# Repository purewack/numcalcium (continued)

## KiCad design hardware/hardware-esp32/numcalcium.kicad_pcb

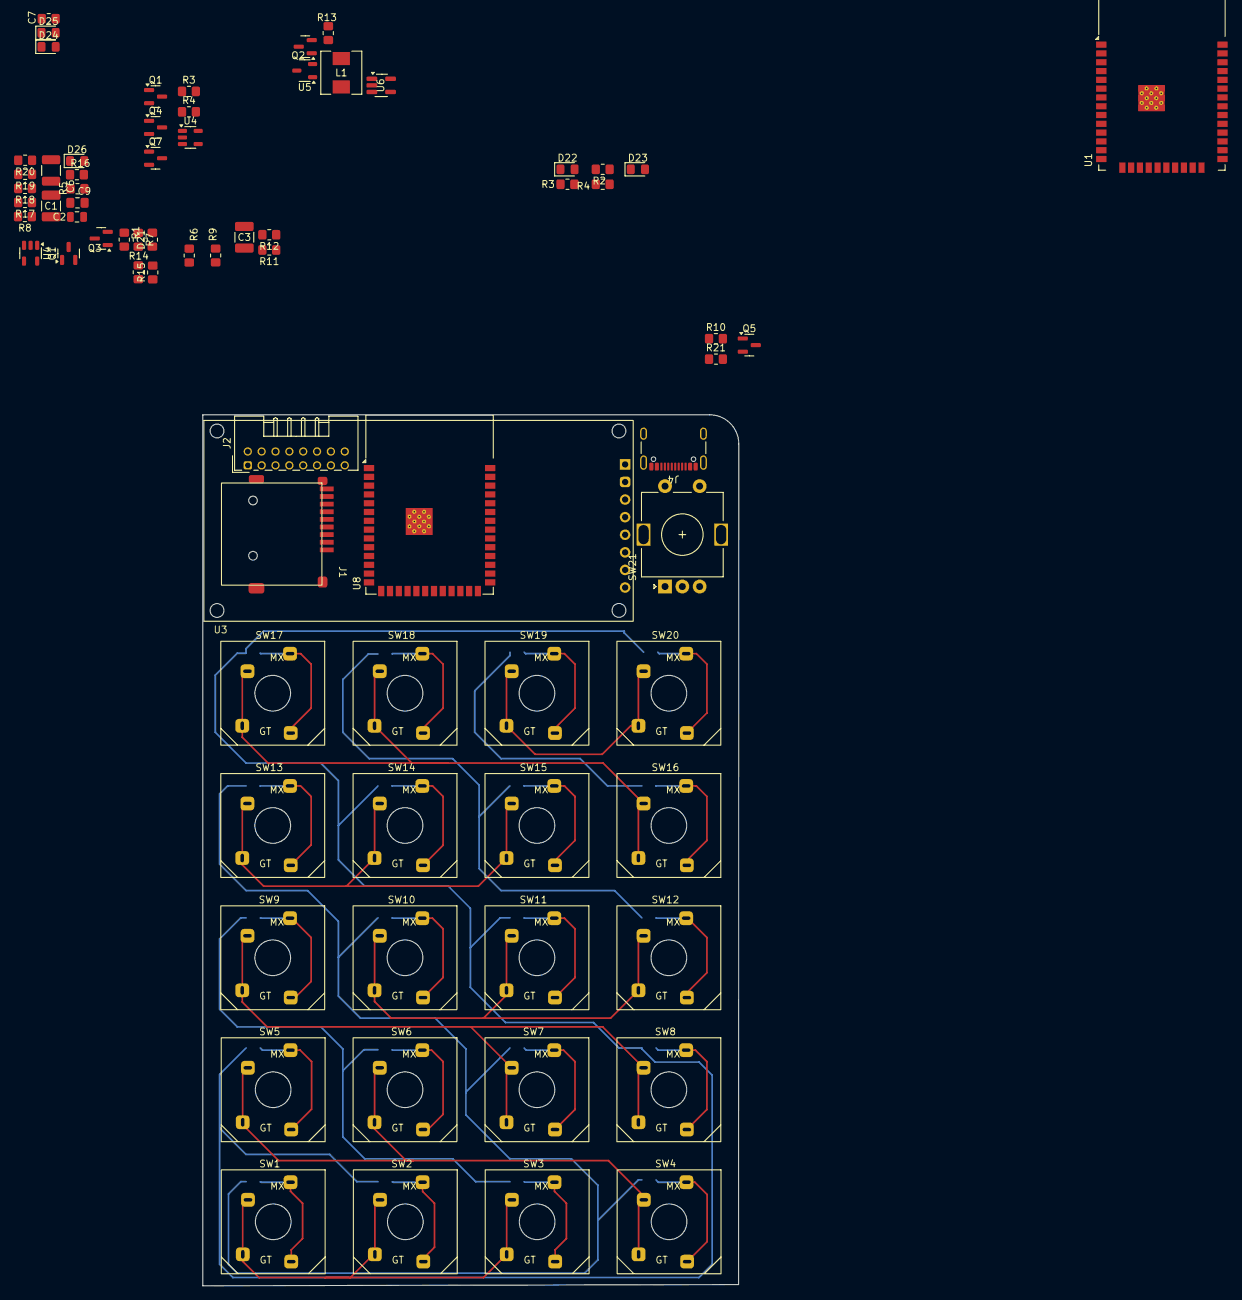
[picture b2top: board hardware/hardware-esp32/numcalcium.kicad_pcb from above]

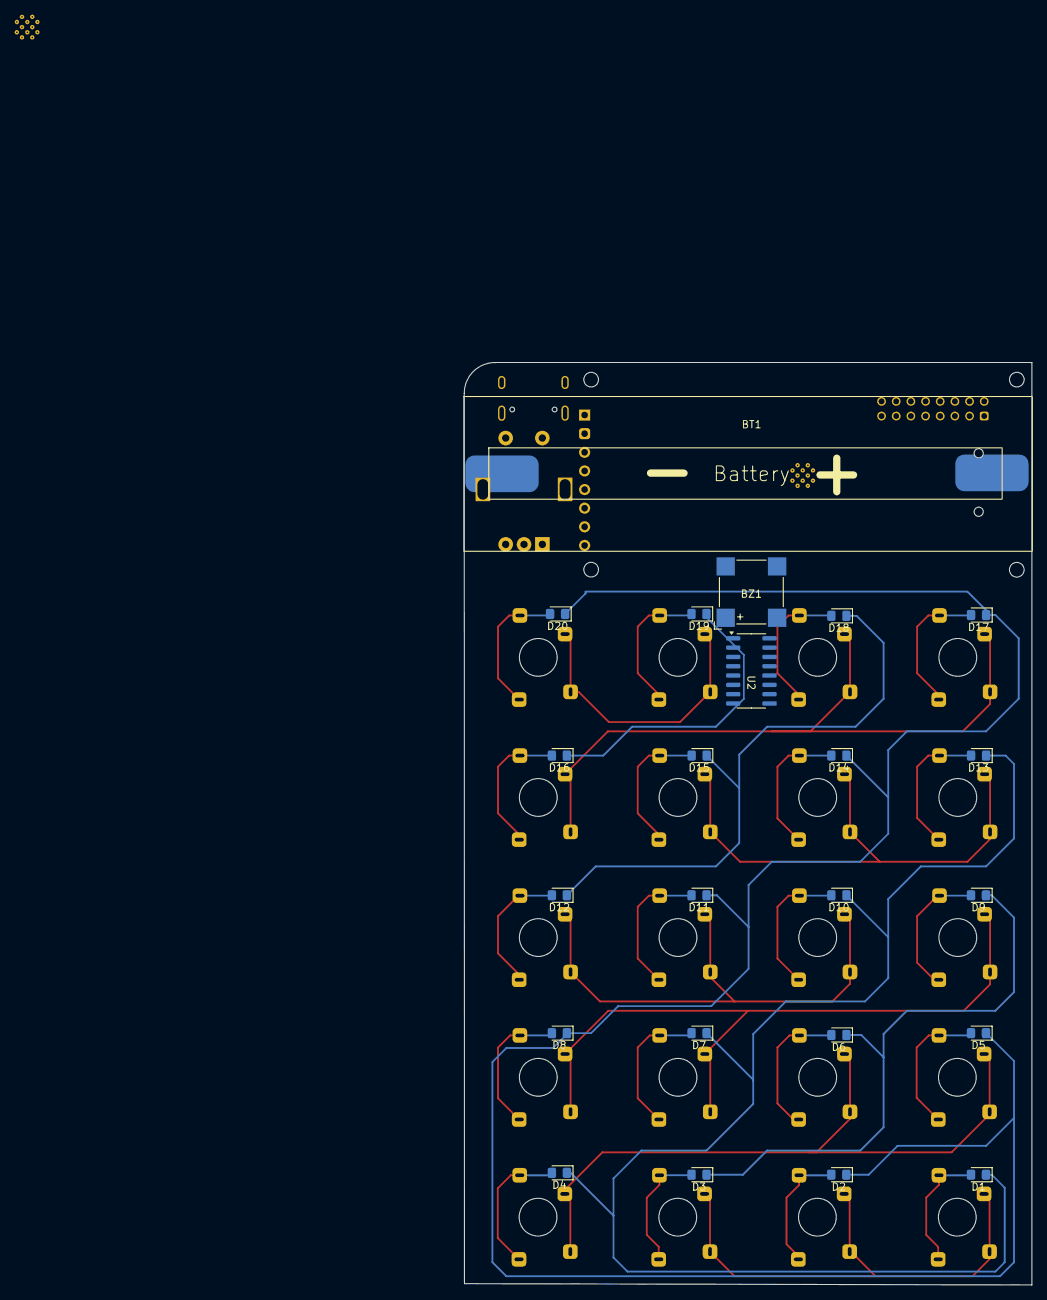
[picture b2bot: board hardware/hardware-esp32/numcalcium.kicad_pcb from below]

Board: 2 copper layers, 77.4 x 125.8 mm, 97 parts (23 on the bottom side), 69 nets.

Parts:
BT1: Battery; LiIon18650
BZ1: Buzzer; MagneticBuzzer_CUI_CMT-8504-100-SMT
C1: 10u; C_1210_3225Metric_Pad1.33x2.70mm_HandSolder
C2: 100n; C_0805_2012Metric
C3: 22u; C_1210_3225Metric_Pad1.33x2.70mm_HandSolder
C6: 22u; R_1210_3225Metric_Pad1.30x2.65mm_HandSolder
C7: 100n; R_0805_2012Metric_Pad1.20x1.40mm_HandSolder
C9: 22u; C_0805_2012Metric_Pad1.18x1.45mm_HandSolder
D1, D2, D3, D4, D5, D6, D7, D8, D9, D10, D11, D12, D13, D14, D15, D16, D17, D18, D19, D20, D22, D23, D24, D25, D26: D; D_0805_2012Metric_Pad1.15x1.40mm_HandSolder
D21: BAT_REV; R_0805_2012Metric_Pad1.20x1.40mm_HandSolder
J1: Micro_SD_Card_Det2; microSD_Short_1
J2: Conn_02x08_Counter_Clockwise; JAE_LY20-16P-DLT1_2x08_P2.00mm_Horizontal
J4: USB_C_Receptacle_USB2.0_16P; USB_C_Receptacle_GCT_USB4105-xx-A_16P_TopMnt_Horizontal
L1: 2u2; L_Chilisin_BMRA00050530
Q1, Q1#2, Q4, Q7: AO3401A; SOT-23
Q2, Q3, Q5: BSS138; SOT-23
R1, R2, R11, R12: 100k; R_0805_2012Metric_Pad1.20x1.40mm_HandSolder
R3, R3#2, R4, R4#2: 5k6; R_0805_2012Metric_Pad1.20x1.40mm_HandSolder
R5: 2k; R_0805_2012Metric_Pad1.20x1.40mm_HandSolder
R6: 220k; R_0805_2012Metric_Pad1.20x1.40mm_HandSolder
R7: 33k; R_0805_2012Metric_Pad1.20x1.40mm_HandSolder
R8, R9, R17, R18, R19, R20: 47k; R_0805_2012Metric_Pad1.20x1.40mm_HandSolder
R10, R15, R21: 10k; R_0805_2012Metric_Pad1.20x1.40mm_HandSolder
R13, R14, R16: 1M; R_0805_2012Metric_Pad1.20x1.40mm_HandSolder
SW1, SW2, SW3, SW4, SW5, SW6, SW7, SW8, SW9, SW10, SW11, SW12, SW13, SW14, SW15, SW16, SW17, SW18, SW19, SW20: SW_Push; Combo_MechanicalSwitch
SW21: Encoder; RotaryEncoder_Alps_EC11E-Switch_Vertical_H20mm
U1: ESP32-WROOM-32D
U2: 74HC595; SOIC-16_3.9x9.9mm_P1.27mm
U3: ISP Display; ST7789 1.9inch module Display
U4, U4#2: LTC4054ES5-4.2; TSOT-23-5
U5: XC6206PxxxMR; SOT-23-3
U6: STI3411A; SOT-23-5_HandSoldering
U8: ESP32-S3-WROOM-1

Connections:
/Power/VBAT_MON: R13.2, R14.1
/Power/VCART: C6.1, C7.1, Q1.3 (D), Q1#2.3 (D)
/Power/VCART_ON: Q1.1 (G), Q1#2.1 (G), R11.2
/Power/VDD_AON: C9.1, L1.2, R6.1, U5.2 (VO)
/Power/VPOW_OFF: Q4.1 (G), R16.2, U6.1 (EN)
B_OK: R2.2, SW21.S1, U1.25 (IO0)
CART_FEED: R12.1, SW19.2, SW20.2, U2.1 (QB)
CART_SENSE: D24.2 (A), R12.2
GND: BT1.2 (-), C1.2, C2.2, C3.2, C6.2, C7.2, C9.2, D21.2 (A), J1.6 (VSS), J1.11 (SHIELD), J4.A1 (GND), J4.A12 (GND), J4.B1 (GND), J4.B12 (GND), Q2.2 (S), Q3.2 (S), Q5.2 (S), Q7.1 (G), R3.2, R3#2.2, R4.2, R4#2.2, R5.2, R9.2, R14.2, SW21.S2, U1.1 (GND), U1.15 (GND), U1.38 (GND), U1.39 (GND), U2.8 (GND), U3.1 (GND), U4.2 (GND), U4#2.2 (GND), U5.1 (GND), U6.2 (GND)
IO_CK: D1.1 (K), D4.1 (K), D7.1 (K), D10.1 (K), D13.1 (K), D16.1 (K), D19.1 (K), D22.1 (K), U1.8 (IO32), U2.11 (SRCLK)
IO_D: D2.1 (K), D5.1 (K), D8.1 (K), D11.1 (K), D14.1 (K), D17.1 (K), D20.1 (K), D23.1 (K), U1.9 (IO33), U2.14 (SER)
IO_OE: Q2.1 (G), U1.12 (IO27), U2.12 (RCLK)
IO_T: D3.1 (K), D6.1 (K), D9.1 (K), D12.1 (K), D15.1 (K), D18.1 (K), D24.1 (K), D25.1 (K), U1.6 (IO34)
unnamed: BT1.1 (+), Q7.3 (D), R7.1
unnamed: BZ1.2 (-), D26.2 (A), Q3.3 (D)
unnamed: D1.2 (A), SW1.1
unnamed: D2.2 (A), SW2.1
unnamed: D3.2 (A), SW3.1
unnamed: D4.2 (A), SW4.1
unnamed: D5.2 (A), SW5.1
unnamed: D6.2 (A), SW6.1
unnamed: D7.2 (A), SW7.1
unnamed: D8.2 (A), SW8.1
unnamed: D9.2 (A), SW9.1
unnamed: D10.2 (A), SW10.1
unnamed: D11.2 (A), SW11.1
unnamed: D12.2 (A), SW12.1
unnamed: D13.2 (A), SW13.1
unnamed: D14.2 (A), SW14.1
unnamed: D15.2 (A), SW15.1
unnamed: D16.2 (A), SW16.1
unnamed: D17.2 (A), SW17.1
unnamed: D18.2 (A), SW18.1
unnamed: D19.2 (A), SW19.1
unnamed: D20.2 (A), SW20.1
unnamed: D21.1 (K), R7.2
unnamed: D22.2 (A), SW21.A
unnamed: D23.2 (A), SW21.B
unnamed: J1.5 (CLK), U1.13 (IO14), U3.3 (CK)
unnamed: J1.3 (CMD), R18.2, U1.23 (IO15), U3.4 (D)
unnamed: J1.7 (DAT0), R19.2, U1.24 (IO2)
unnamed: J1.8 (DAT1), R20.2, U1.26 (IO4), U3.6 (DC)
unnamed: J1.1 (DAT2), R8.2, U1.14 (IO12)
unnamed: J1.2 (DAT3/CD), R17.2, U1.16 (IO13)
unnamed: J4.A5 (CC1), R3.1, R3#2.1
unnamed: J4.B5 (CC2), R4.1, R4#2.1
unnamed: C3.1, Q1.2 (S), Q1#2.2 (S), Q4.2 (S), Q7.2 (S), R11.1, R13.1, R16.1, U4.3 (BAT), U4#2.3 (BAT), U6.4 (VIN)
unnamed: Q2.3 (D), R1.2, U2.13 (~OE)
unnamed: Q3.1 (G), R15.2
unnamed: Q4.3 (D), U5.3 (VI)
unnamed: Q5.3 (D), U3.8 (LIGHT)
unnamed: Q5.1 (G), R10.2
unnamed: R21.1, U1.3 (EN)
unnamed: U1.28 (IO17), U3.7 (CS)
unnamed: R10.1, U1.5 (SENSOR_VN)
unnamed: SW16.2, SW17.2, SW18.2, U2.2 (QC)
unnamed: SW13.2, SW14.2, SW15.2, U2.3 (QD)
unnamed: SW10.2, SW11.2, SW12.2, U2.4 (QE)
unnamed: SW7.2, SW8.2, SW9.2, U2.5 (QF)
unnamed: SW4.2, SW5.2, SW6.2, U2.6 (QG)
unnamed: SW1.2, SW2.2, SW3.2, U2.7 (QH)
unnamed: R5.1, U4.5 (PROG), U4#2.5 (PROG)
unnamed: C1.1, C2.1, J4.A4 (VBUS), J4.A9 (VBUS), J4.B4 (VBUS), J4.B9 (VBUS), U4.4 (V_{CC}), U4#2.4 (V_{CC})
unnamed: R6.2, R9.1
unnamed: L1.1, U6.3 (LX)
unnamed: U8.1 (GND), U8.40 (GND), U8.41 (GND)
SD_FEED: SW21.C, U2.15 (QA)
SD_SENSE: D25.2 (A), J1.9 (DET_B)
VDD: BZ1.1 (+), D26.1 (K), J1.4 (VDD), R1.1, R8.1, R17.1, R18.1, R19.1, R20.1, R21.2, U1.2 (VDD), U2.10 (~SRCLR), U2.16 (VCC), U3.2 (VDD)

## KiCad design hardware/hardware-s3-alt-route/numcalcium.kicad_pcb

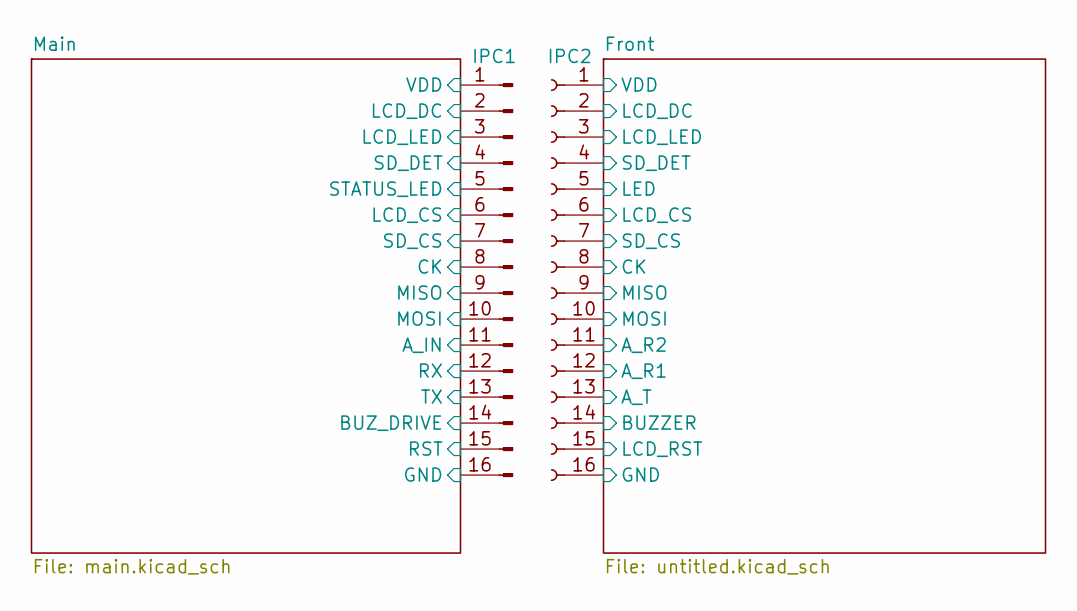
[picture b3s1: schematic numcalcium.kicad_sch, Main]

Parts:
IPC1: Conn_01x16_Pin; PinHeader_1x16_P2.54mm_Vertical
IPC2: Conn_01x16_Socket; PinSocket_1x16_P2.54mm_Vertical

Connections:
/Front/A_R1: IPC2.12; also elsewhere on the board
/Front/A_R2: IPC2.11; also elsewhere on the board
/Front/A_T: IPC2.13; also elsewhere on the board
/Front/BUZZER: IPC2.14; also elsewhere on the board
/Front/CK: IPC2.8; also elsewhere on the board
/Front/LCD_CS: IPC2.6; also elsewhere on the board
/Front/LCD_DC: IPC2.2; also elsewhere on the board
/Front/LCD_LED: IPC2.3; also elsewhere on the board
/Front/LCD_RST: IPC2.15; also elsewhere on the board
/Front/LED: IPC2.5; also elsewhere on the board
/Front/MISO: IPC2.9; also elsewhere on the board
/Front/MOSI: IPC2.10; also elsewhere on the board
/Front/SD_CS: IPC2.7; also elsewhere on the board
/Front/SD_DET: IPC2.4; also elsewhere on the board
/Front/VDD: IPC2.1; also elsewhere on the board
/Main/A_IN: IPC1.11; also elsewhere on the board
/Main/BUZ_DRIVE: IPC1.14; also elsewhere on the board
/Main/CK: IPC1.8; also elsewhere on the board
/Main/LCD_CS: IPC1.6; also elsewhere on the board
/Main/LCD_DC: IPC1.2; also elsewhere on the board
/Main/LCD_LED: IPC1.3; also elsewhere on the board
/Main/MISO: IPC1.9; also elsewhere on the board
/Main/MOSI: IPC1.10; also elsewhere on the board
/Main/RX: IPC1.12; also elsewhere on the board
/Main/SD_CS: IPC1.7; also elsewhere on the board
/Main/SD_DET: IPC1.4; also elsewhere on the board
/Main/STATUS_LED: IPC1.5; also elsewhere on the board
/Main/TX: IPC1.13; also elsewhere on the board
GND: IPC1.16, IPC2.16; also elsewhere on the board
RST: IPC1.15; also elsewhere on the board
VDD: IPC1.1; also elsewhere on the board

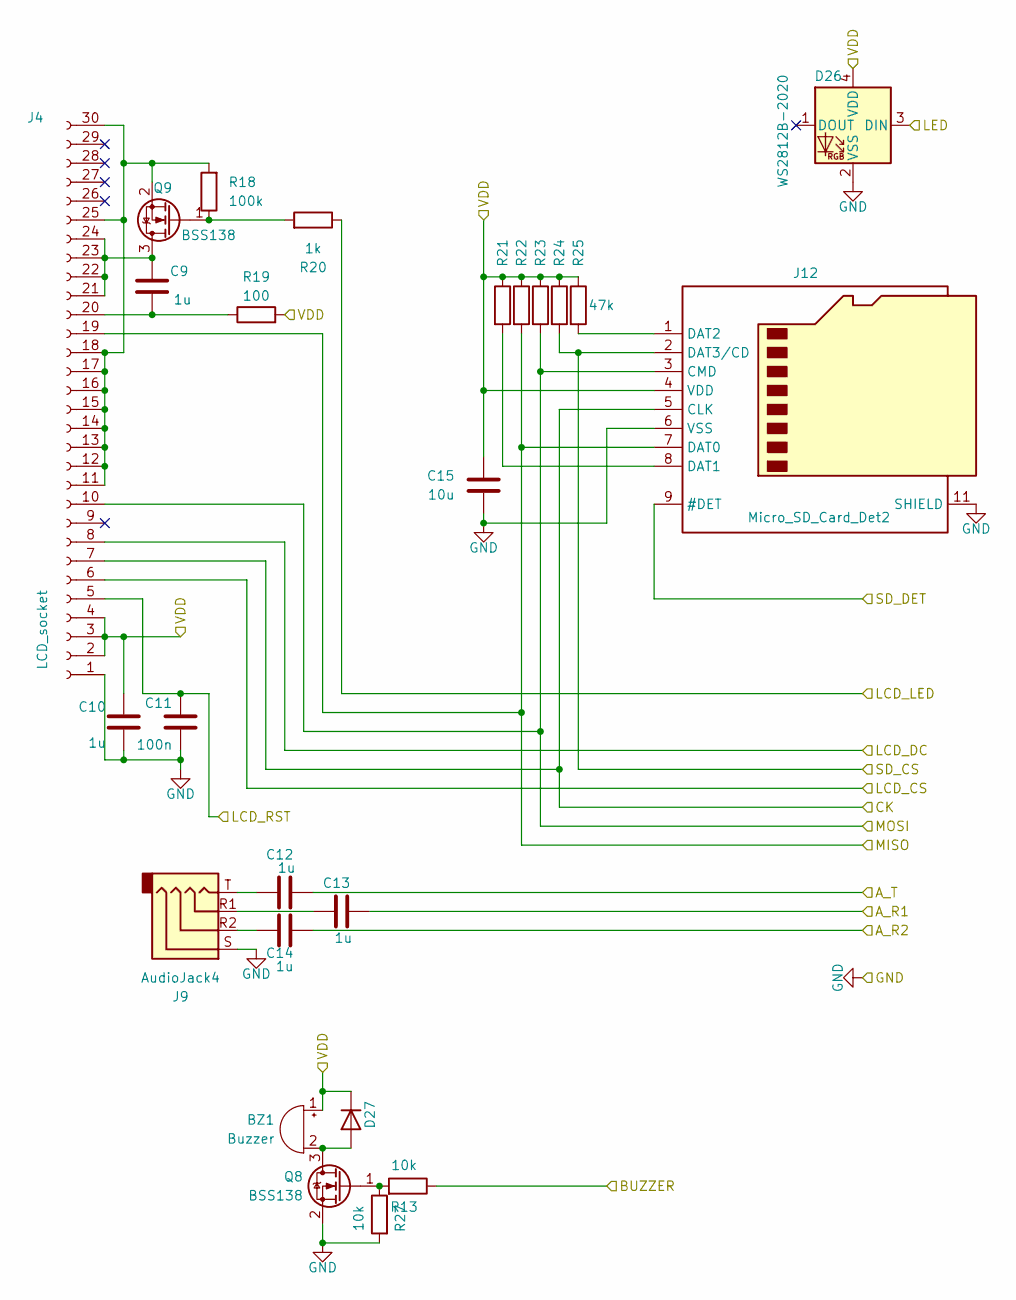
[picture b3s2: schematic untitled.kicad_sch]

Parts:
BZ1: Buzzer; MagneticBuzzer_CUI_CMT-8504-100-SMT
C9, C10, C12, C13, C14: 1u; C_0805_2012Metric
C11: 100n; C_0805_2012Metric
C15: 10u; C_0805_2012Metric
D26: WS2812B-2020; LED_WS2812B-2020_PLCC4_2.0x2.0mm
D27: D; D_0805_2012Metric_Pad1.15x1.40mm_HandSolder
J4: LCD_socket; Hirose_FH12-30S-0.5SH_1x30-1MP_P0.50mm_Horizontal
J9: AudioJack4; Jack_3.5mm_PJ320D_Horizontal
J12: Micro_SD_Card_Det2; microSD_Short_1
Q8, Q9: BSS138; SOT-23
R13, R27: 10k; R_0805_2012Metric_Pad1.20x1.40mm_HandSolder
R18: 100k; R_0805_2012Metric_Pad1.20x1.40mm_HandSolder
R19: 100; R_0805_2012Metric_Pad1.20x1.40mm_HandSolder
R20: 1k; R_0805_2012Metric_Pad1.20x1.40mm_HandSolder
R21, R22, R23, R24, R25: 47k; R_0805_2012Metric_Pad1.20x1.40mm_HandSolder

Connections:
/Front/A_R1: C13.2; also elsewhere on the board
/Front/A_R2: C14.2; also elsewhere on the board
/Front/A_T: C12.2; also elsewhere on the board
/Front/BUZZER: R13.1; also elsewhere on the board
/Front/CK: J4.7, J12.5 (CLK); also elsewhere on the board
/Front/LCD_CS: J4.6; also elsewhere on the board
/Front/LCD_DC: J4.8; also elsewhere on the board
/Front/LCD_LED: R20.1; also elsewhere on the board
/Front/LCD_RST: C11.1, J4.5; also elsewhere on the board
/Front/LED: D26.3 (DIN); also elsewhere on the board
/Front/MISO: J4.19, J12.7 (DAT0), R22.2; also elsewhere on the board
/Front/MOSI: J4.10, J12.3 (CMD), R23.2; also elsewhere on the board
/Front/SD_CS: J12.2 (DAT3/CD), R24.2; also elsewhere on the board
/Front/SD_DET: J12.9 (#DET); also elsewhere on the board
/Front/VDD: BZ1.1 (+), C10.1, C15.1, D26.4 (VDD), D27.1 (K), J4.2, J4.3, J4.4, J12.4 (VDD), R19.2, R21.1, R22.1, R23.1, R24.1, R25.1; also elsewhere on the board
GND: C10.2, C11.2, C15.2, D26.2 (VSS), J4.1, J9.S, J12.6 (VSS), J12.11 (SHIELD), Q8.2 (S), R27.2; also elsewhere on the board
unnamed: BZ1.2 (-), D27.2 (A), Q8.3 (D)
unnamed: C12.1, J9.T
unnamed: C13.1, J9.R1
unnamed: C14.1, J9.R2
unnamed: J4.11, J4.12, J4.13, J4.14, J4.15, J4.16, J4.17, J4.18, J4.25, J4.30, Q9.2 (S), R18.2
unnamed: C9.2, J4.20, R19.1
unnamed: C9.1, J4.21, J4.22, J4.23, J4.24, Q9.3 (D)
unnamed: J12.8 (DAT1), R21.2
unnamed: J12.1 (DAT2), R25.2
unnamed: Q8.1 (G), R13.2, R27.1
unnamed: Q9.1 (G), R18.1, R20.2

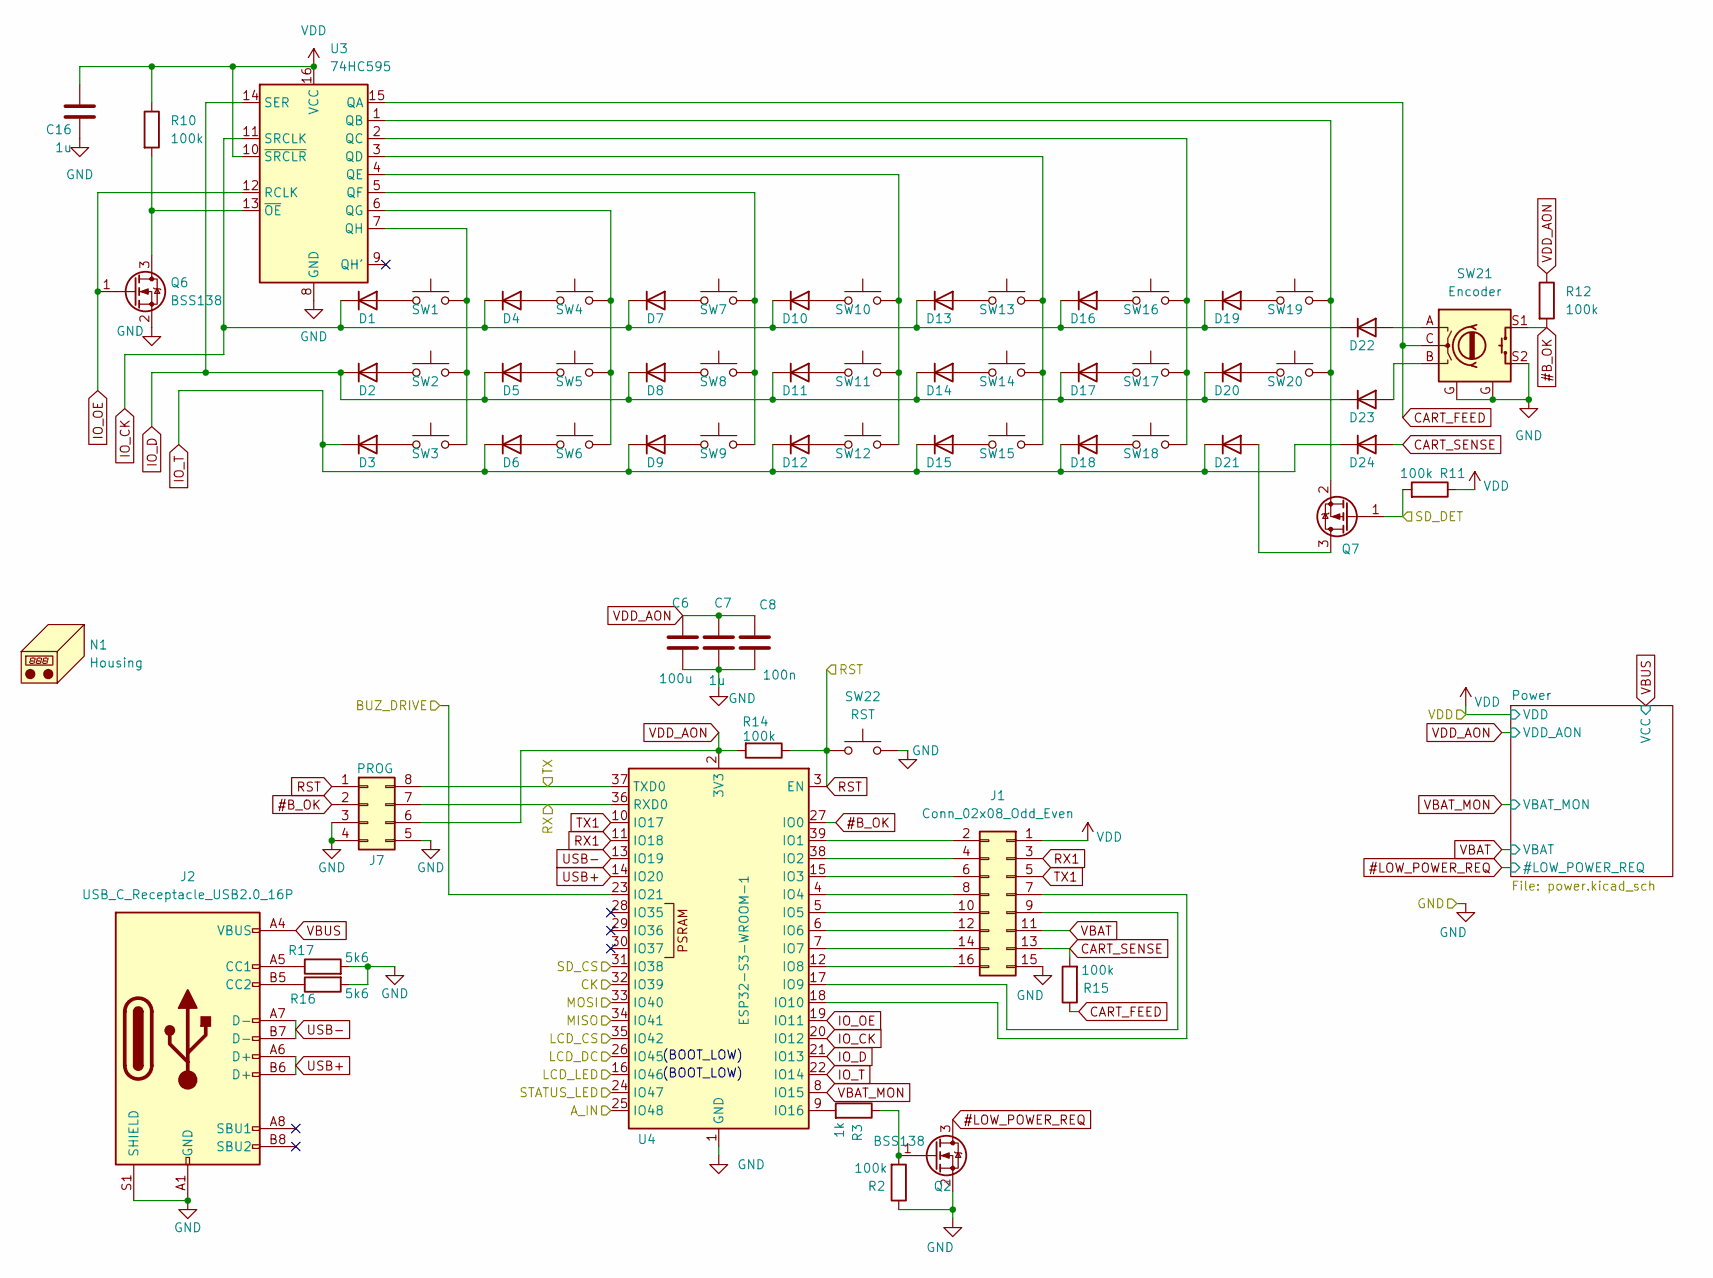
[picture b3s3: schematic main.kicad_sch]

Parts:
C6: 100u; C_Elec_5x5.4
C7: 1u; C_1206_3216Metric
C8: 100n; R_0805_2012Metric_Pad1.20x1.40mm_HandSolder
C16: 1u; R_0805_2012Metric
D1, D2, D3, D4, D5, D6, D7, D8, D9, D10, D11, D12, D13, D14, D15, D16, D17, D18, D19, D20, D21, D22, D23, D24: D; D_0805_2012Metric_Pad1.15x1.40mm_HandSolder
J1: Conn_02x08_Odd_Even; IDC-Header_2x08_P2.54mm_Horizontal
J2: USB_C_Receptacle_USB2.0_16P; USB_C_Receptacle_GCT_USB4105-xx-A_16P_TopMnt_Horizontal
J7: PROG; PinHeader_2x04_P1.27mm_Vertical_SMD
N1: Housing; OSHW-Symbol_6.7x6mm_SilkScreen
Q2, Q6: BSS138; SOT-23
Q7: AO3401A; SOT-23
R2, R10, R11, R12, R14, R15: 100k; R_0805_2012Metric_Pad1.20x1.40mm_HandSolder
R3: 1k; R_0805_2012Metric_Pad1.20x1.40mm_HandSolder
R16, R17: 5k6; R_0805_2012Metric_Pad1.20x1.40mm_HandSolder
SW1, SW2, SW3, SW4, SW5, SW6, SW7, SW8, SW9, SW10, SW11, SW12, SW13, SW14, SW15, SW16, SW17, SW18, SW19, SW20: SW_Push; Combo_MechanicalSwitch
SW21: Encoder; RotaryEncoder_Alps_EC11E-Switch_Vertical_H20mm
SW22: RST; SW_SPST_PTS647_Sx38
U3: 74HC595; SOIC-16_3.9x9.9mm_P1.27mm
U4: ESP32-S3-WROOM-1; ESP32-S3-WROOM-1-Compact-Court

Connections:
#B_OK: J7.2, R12.2, SW21.S1, U4.27 (IO0)
#LOW_POWER_REQ: Q2.3 (D); also elsewhere on the board
/Main/A_IN: U4.25 (IO48); also elsewhere on the board
/Main/BUZ_DRIVE: U4.23 (IO21); also elsewhere on the board
/Main/CK: U4.32 (IO39); also elsewhere on the board
/Main/LCD_CS: U4.35 (IO42); also elsewhere on the board
/Main/LCD_DC: U4.26 (IO45); also elsewhere on the board
/Main/LCD_LED: U4.16 (IO46); also elsewhere on the board
/Main/MISO: U4.34 (IO41); also elsewhere on the board
/Main/MOSI: U4.33 (IO40); also elsewhere on the board
/Main/RX: J7.7, U4.36 (RXD0); also elsewhere on the board
/Main/SD_CS: U4.31 (IO38); also elsewhere on the board
/Main/SD_DET: Q7.1 (G), R11.2; also elsewhere on the board
/Main/STATUS_LED: U4.24 (IO47); also elsewhere on the board
/Main/TX: J7.8, U4.37 (TXD0); also elsewhere on the board
CART_FEED: R15.1, SW21.C, U3.15 (QA)
CART_SENSE: D24.2 (A), J1.13, R15.2
GND: C6.2, C7.2, C8.2, C16.2, J1.15, J2.A1 (GND), J2.A12 (GND), J2.B1 (GND), J2.B12 (GND), J2.S1 (SHIELD), J7.3, J7.4, J7.5, Q2.2 (S), Q6.2 (S), R2.1, R16.2, R17.2, SW21.G (MOUNT), SW21.S2, SW22.2, U3.8 (GND), U4.1 (GND), U4.40 (GND), U4.41 (GND); also elsewhere on the board
IO_CK: D1.1 (K), D4.1 (K), D7.1 (K), D10.1 (K), D13.1 (K), D16.1 (K), D19.1 (K), D22.1 (K), U3.11 (SRCLK), U4.20 (IO12)
IO_D: D2.1 (K), D5.1 (K), D8.1 (K), D11.1 (K), D14.1 (K), D17.1 (K), D20.1 (K), D23.1 (K), U3.14 (SER), U4.21 (IO13)
IO_OE: Q6.1 (G), U3.12 (RCLK), U4.19 (IO11)
IO_T: D3.1 (K), D6.1 (K), D9.1 (K), D12.1 (K), D15.1 (K), D18.1 (K), D21.1 (K), D24.1 (K), U4.22 (IO14)
unnamed: D1.2 (A), SW1.1
unnamed: D2.2 (A), SW2.1
unnamed: D3.2 (A), SW3.1
unnamed: D4.2 (A), SW4.1
unnamed: D5.2 (A), SW5.1
unnamed: D6.2 (A), SW6.1
unnamed: D7.2 (A), SW7.1
unnamed: D8.2 (A), SW8.1
unnamed: D9.2 (A), SW9.1
unnamed: D10.2 (A), SW10.1
unnamed: D11.2 (A), SW11.1
unnamed: D12.2 (A), SW12.1
unnamed: D13.2 (A), SW13.1
unnamed: D14.2 (A), SW14.1
unnamed: D15.2 (A), SW15.1
unnamed: D16.2 (A), SW16.1
unnamed: D17.2 (A), SW17.1
unnamed: D18.2 (A), SW18.1
unnamed: D19.2 (A), SW19.1
unnamed: D20.2 (A), SW20.1
unnamed: D21.2 (A), Q7.3 (D)
unnamed: D22.2 (A), SW21.A
unnamed: D23.2 (A), SW21.B
unnamed: J1.2, U4.39 (IO1)
unnamed: J1.4, U4.38 (IO2)
unnamed: J1.6, U4.15 (IO3)
unnamed: J1.7, U4.18 (IO10)
unnamed: J1.8, U4.4 (IO4)
unnamed: J1.9, U4.17 (IO9)
unnamed: J1.10, U4.5 (IO5)
unnamed: J1.12, U4.6 (IO6)
unnamed: J1.14, U4.7 (IO7)
unnamed: J1.16, U4.12 (IO8)
unnamed: J2.A5 (CC1), R17.1
unnamed: J2.B5 (CC2), R16.1
unnamed: Q2.1 (G), R2.2, R3.1
unnamed: Q6.3 (D), R10.2, U3.13 (~OE)
unnamed: Q7.2 (S), SW19.2, SW20.2, U3.1 (QB)
unnamed: SW16.2, SW17.2, SW18.2, U3.2 (QC)
unnamed: SW13.2, SW14.2, SW15.2, U3.3 (QD)
unnamed: SW10.2, SW11.2, SW12.2, U3.4 (QE)
unnamed: SW7.2, SW8.2, SW9.2, U3.5 (QF)
unnamed: SW4.2, SW5.2, SW6.2, U3.6 (QG)
unnamed: SW1.2, SW2.2, SW3.2, U3.7 (QH)
unnamed: R3.2, U4.9 (IO16)
RST: J7.1, R14.1, SW22.1, U4.3 (EN); also elsewhere on the board
RX1: J1.3, U4.11 (IO18)
TX1: J1.5, U4.10 (IO17)
USB+: J2.A6 (D+), J2.B6 (D+), U4.14 (IO20)
USB-: J2.A7 (D-), J2.B7 (D-), U4.13 (IO19)
VBAT: J1.11; also elsewhere on the board
VBAT_MON: U4.8 (IO15); also elsewhere on the board
VBUS: J2.A4 (VBUS), J2.A9 (VBUS), J2.B4 (VBUS), J2.B9 (VBUS); also elsewhere on the board
VDD: C16.1, J1.1, R10.1, R11.1, U3.10 (~SRCLR), U3.16 (VCC); also elsewhere on the board
VDD_AON: C6.1, C7.1, C8.1, J7.6, R12.1, R14.2, U4.2 (3V3); also elsewhere on the board

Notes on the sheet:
(BOOT_LOW)

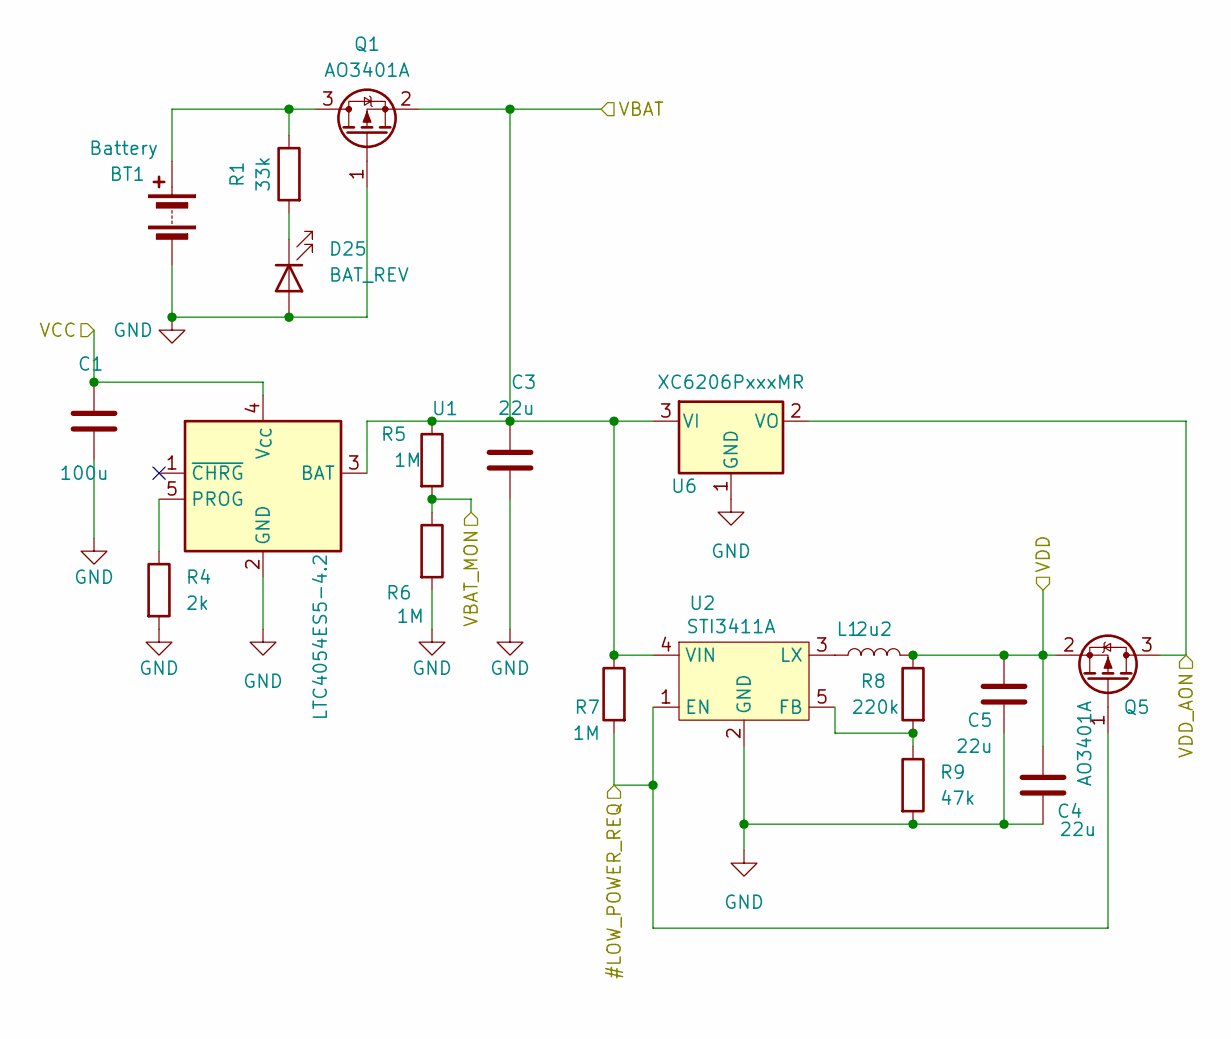
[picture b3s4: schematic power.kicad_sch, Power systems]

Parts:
BT1: Battery; LiIon18650
C1: 100u; C_1210_3225Metric
C3: 22u; C_1210_3225Metric_Pad1.33x2.70mm_HandSolder
C4: 22u; C_0805_2012Metric_Pad1.18x1.45mm_HandSolder
C5: 22u; R_1210_3225Metric_Pad1.30x2.65mm_HandSolder
D25: BAT_REV; R_0805_2012Metric_Pad1.20x1.40mm_HandSolder
L1: 2u2; L_Chilisin_BMRA00050530
Q1, Q5: AO3401A; SOT-23
R1: 33k; R_0805_2012Metric_Pad1.20x1.40mm_HandSolder
R4: 2k; R_0805_2012Metric_Pad1.20x1.40mm_HandSolder
R5, R6, R7: 1M; R_0805_2012Metric_Pad1.20x1.40mm_HandSolder
R8: 220k; R_0805_2012Metric_Pad1.20x1.40mm_HandSolder
R9: 47k; R_0805_2012Metric_Pad1.20x1.40mm_HandSolder
U1: LTC4054ES5-4.2; TSOT-23-5
U2: STI3411A; TSOT-23-5
U6: XC6206PxxxMR; SOT-23-3

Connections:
#LOW_POWER_REQ: Q5.1 (G), R7.2, U2.1 (EN); also elsewhere on the board
GND: BT1.2 (-), C1.2, C3.2, C4.2, C5.2, D25.2 (A), Q1.1 (G), R4.2, R6.2, R9.2, U1.2 (GND), U2.2 (GND), U6.1 (GND); also elsewhere on the board
unnamed: BT1.1 (+), Q1.3 (D), R1.1
unnamed: D25.1 (K), R1.2
unnamed: R4.1, U1.5 (PROG)
unnamed: R8.2, R9.1, U2.5 (FB)
unnamed: L1.1, U2.3 (LX)
VBAT: C3.1, Q1.2 (S), R5.1, R7.1, U1.3 (BAT), U2.4 (VIN), U6.3 (VI); also elsewhere on the board
VBAT_MON: R5.2, R6.1; also elsewhere on the board
VBUS: C1.1, U1.4 (V_{CC}); also elsewhere on the board
VDD: C4.1, C5.1, L1.2, Q5.2 (S), R8.1; also elsewhere on the board
VDD_AON: Q5.3 (D), U6.2 (VO); also elsewhere on the board

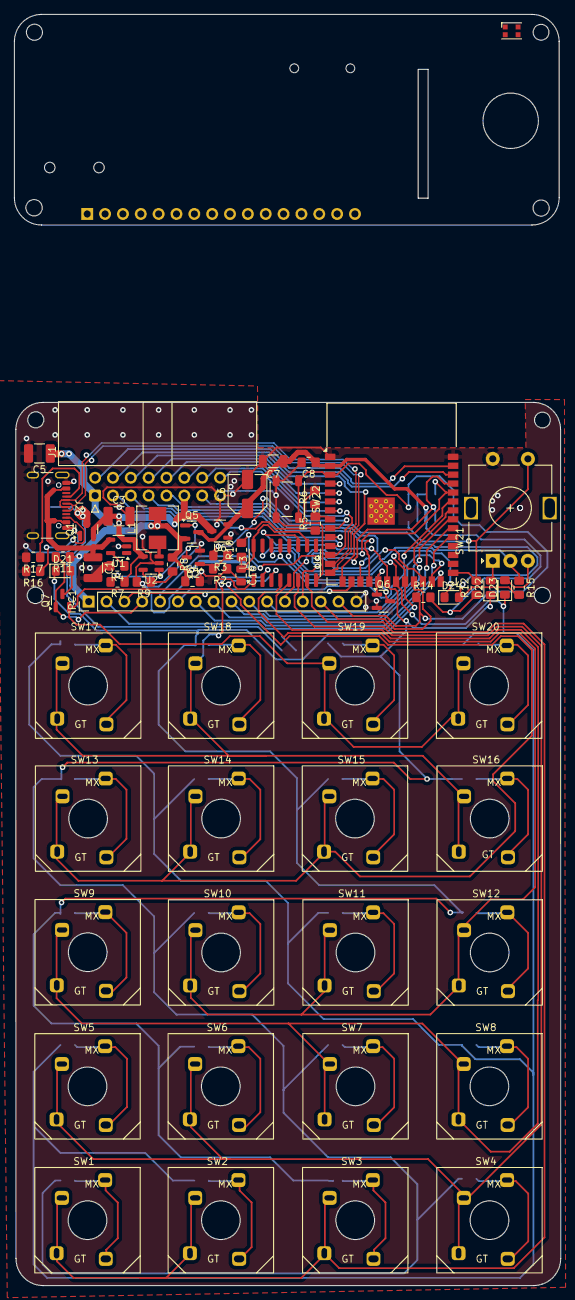
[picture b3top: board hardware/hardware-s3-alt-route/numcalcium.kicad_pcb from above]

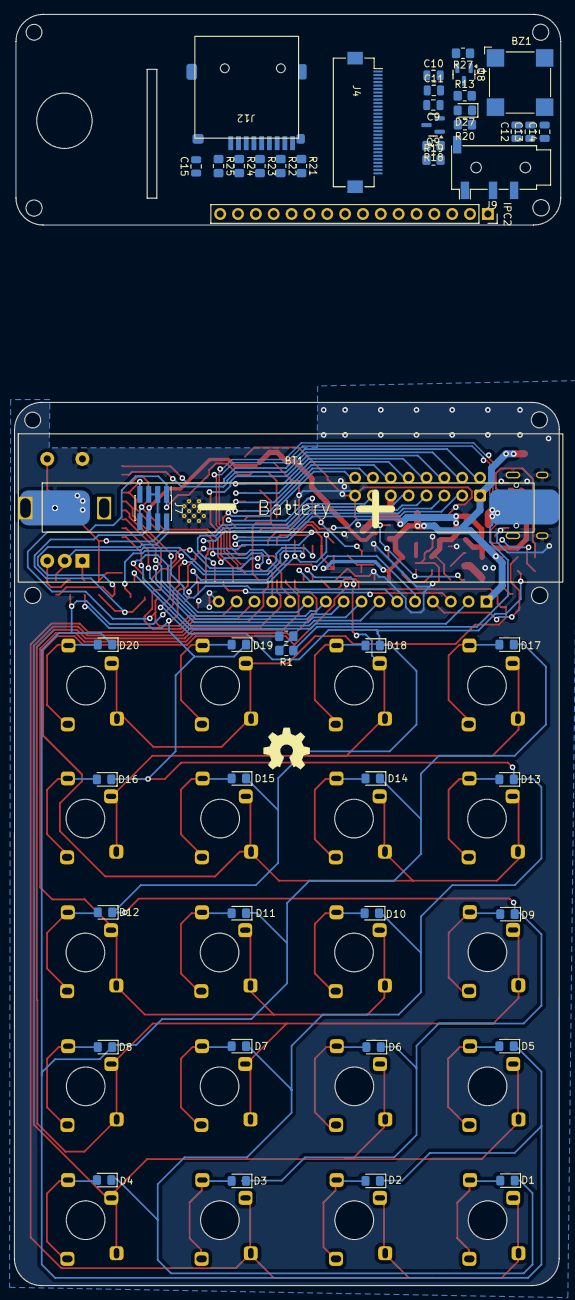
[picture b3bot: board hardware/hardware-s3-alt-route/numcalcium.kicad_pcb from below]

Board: 2 copper layers, 77.7 x 180.9 mm, 114 parts (50 on the bottom side), 108 nets.

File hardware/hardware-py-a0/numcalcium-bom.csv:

"Reference","Value","Datasheet","Footprint","Qty","DNP"
"BT1","Battery","~","footprints:LiIon18650","1",""
"BZ1","Buzzer","~","Buzzer_Beeper:MagneticBuzzer_CUI_CMT-8504-100-SMT","1",""
"C1,C6","100u","~","-- mixed values --","2",""
"C2,C3,C5","22u","~","-- mixed values --","3",""
"C7,C9,C10,C12,C13","1u","~","-- mixed values --","5",""
"C8,C11","100n","~","-- mixed values --","2",""
"C15","10u","~","Capacitor_SMD:C_0805_2012Metric","1",""
"D1,D2,D3,D4,D5,D6,D7,D8,D9,D10,D11,D12,D13,D14,D15,D16,D17,D18,D19,D20,D21,D22,D23,D24,D27","D","~","Diode_SMD:D_0805_2012Metric_Pad1.15x1.40mm_HandSolder","25",""
"D25","BAT_REV","~","Resistor_SMD:R_0805_2012Metric_Pad1.20x1.40mm_HandSolder","1",""
"D26","WS2812B-2020","https://cdn-shop.adafruit.com/product-files/4684/4684_WS2812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","LED_SMD:LED_WS2812B-2020_PLCC4_2.0x2.0mm","1",""
"D28","MBR0520LT","http://www.onsemi.com/pub_link/Collateral/MBR0520LT1-D.PDF","Diode_SMD:D_SOD-123","1",""
"IPC1","Conn_01x16_Pin","~","Connector_PinHeader_2.54mm:PinHeader_1x15_P2.54mm_Vertical","1",""
"IPC2","Conn_01x16_Socket","~","footprints:PinSocket_1x15_P2.54mm_Vertical_Pads","1",""
"J1","Conn_02x08_Odd_Even","~","footprints:IDC-Header_2x08_P2.54mm_Horizontal","1",""
"J2","USB_C_Receptacle_USB2.0_16P","https://www.usb.org/sites/default/files/documents/usb_type-c.zip","Connector_USB:USB_C_Receptacle_GCT_USB4105-xx-A_16P_TopMnt_Horizontal","1",""
"J3","Conn_02x04_Odd_Even","~","Connector_PinHeader_1.27mm:PinHeader_2x04_P1.27mm_Vertical_SMD","1",""
"J4","LCD_socket","~","Connector_FFC-FPC:Hirose_FH12-30S-0.5SH_1x30-1MP_P0.50mm_Horizontal","1",""
"J9","AudioJack4","~","footprints:Jack_3.5mm_PJ320D_Horizontal","1",""
"J12","Micro_SD_Card_Det2","https://www.hirose.com/en/product/document?clcode=&productna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","footprints:microSD_Short_1","1",""
"L1","2u2","~","Inductor_SMD:L_Chilisin_BMRA00050530","1",""
"Q1,Q3,Q7","AO3401A","http://www.aosmd.com/pdfs/datasheet/AO3401A.pdf","Package_TO_SOT_SMD:SOT-23","3",""
"Q6,Q8,Q9","BSS138","https://www.onsemi.com/pub/Collateral/BSS138-D.PDF","Package_TO_SOT_SMD:SOT-23","3",""
"R1","33k","~","Resistor_SMD:R_0805_2012Metric_Pad1.20x1.40mm_HandSolder","1",""
"R2,R10,R11,R12,R14,R15,R18","100k","~","Resistor_SMD:R_0805_2012Metric_Pad1.20x1.40mm_HandSolder","7",""
"R3,R5,R6","1M","~","Resistor_SMD:R_0805_2012Metric_Pad1.20x1.40mm_HandSolder","3",""
"R4","2k","~","Resistor_SMD:R_0805_2012Metric_Pad1.20x1.40mm_HandSolder","1",""
"R8","220k","~","Resistor_SMD:R_0805_2012Metric_Pad1.20x1.40mm_HandSolder","1",""
"R9,R21,R22,R23,R24,R25","47k","~","Resistor_SMD:R_0805_2012Metric_Pad1.20x1.40mm_HandSolder","6",""
"R13,R27","10k","~","Resistor_SMD:R_0805_2012Metric_Pad1.20x1.40mm_HandSolder","2",""
"R16,R17","5k6","~","Resistor_SMD:R_0805_2012Metric_Pad1.20x1.40mm_HandSolder","2",""
"R19","100","~","Resistor_SMD:R_0805_2012Metric_Pad1.20x1.40mm_HandSolder","1",""
"R20","1k","~","Resistor_SMD:R_0805_2012Metric_Pad1.20x1.40mm_HandSolder","1",""
"SW1,SW2,SW3,SW4,SW5,SW6,SW7,SW8,SW9,SW10,SW11,SW12,SW13,SW14,SW15,SW16,SW17,SW18,SW19,SW20","SW_Push","~","footprints:Combo_MechanicalSwitch","20",""
"SW21","Encoder","~","footprints:RotaryEncoder_Alps_EC11E-Switch_Vertical_H20mm","1",""
"SW22","RST","~","Button_Switch_SMD:SW_SPST_PTS647_Sx38","1",""
"U1","LTC4054ES5-4.2","https://www.analog.com/media/en/technical-documentation/data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","Package_TO_SOT_SMD:TSOT-23-5","1",""
"U2","STI3411A","","Package_TO_SOT_SMD:TSOT-23-5","1",""
"U3","74HC595","http://www.ti.com/lit/ds/symlink/sn74hc595.pdf","Package_SO:SOIC-16_3.9x9.9mm_P1.27mm","1",""
"U4","ESP32-S3-WROOM-1","https://www.espressif.com/sites/default/files/documentation/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","footprints:ESP32-S3-WROOM-1-Compact-Court","1",""
"U6","XC6206PxxxMR","https://www.torexsemi.com/file/xc6206/XC6206.pdf","Package_TO_SOT_SMD:SOT-23-3","1",""

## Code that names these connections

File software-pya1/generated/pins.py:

from micropython import const

LCD_CS = const(42)
SD_CS = const(38)
LCD_DC = const(46)
LEDS = const(45)
LCD_LED = const(9)
BUZZER = const(10)
A_OUT_L = const(47)
A_OUT_R = const(48)
SLEEP_REQ = const(16)
VBAT_MON = const(15)
CHR_STATE = const(21)
CK = const(39)
MOSI = const(40)
MISO = const(41)
RX1 = const(18)
TX1 = const(17)
RX0 = const(44)
TX0 = const(43)
PORT1 = const(1)
PORT2 = const(2)
PORT3 = const(3)
PORT4 = const(4)
PORT5 = const(5)
PORT6 = const(6)
PORT7 = const(7)
PORT8 = const(8)
PORT9 = const(17)
PORT10 = const(18)
PORT11 = const(43)
PORT12 = const(44)
PORT_SCL = const(44)
PORT_SDA = const(43)
IO_OE = const(11)
IO_CK = const(12)
IO_DD = const(13)
IO_TT = const(14)
B_OK = const(0)
